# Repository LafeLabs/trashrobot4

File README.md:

# Trash Robot

- [arduinocode](arduinocode/)
- [circuitboards](circuitboards/)
- [samtec](samtec/)
- [power](power/)
- [dualhbridge](dualhbridge/)
- [enclosure](enclosure/)
- [unoshield](unoshield/)

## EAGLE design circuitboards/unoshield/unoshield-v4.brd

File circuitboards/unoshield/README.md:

# UNO Shield

- photo of board
- bill of materials excel file
- bill of materials html table
- digikey bom link
- links to arduino codes

[unoshield-v4.brd](unoshield-v4.brd)

[unoshield-v4.sch](unoshield-v4.sch)

[link up a level../](../)

[editor.php](editor.php)

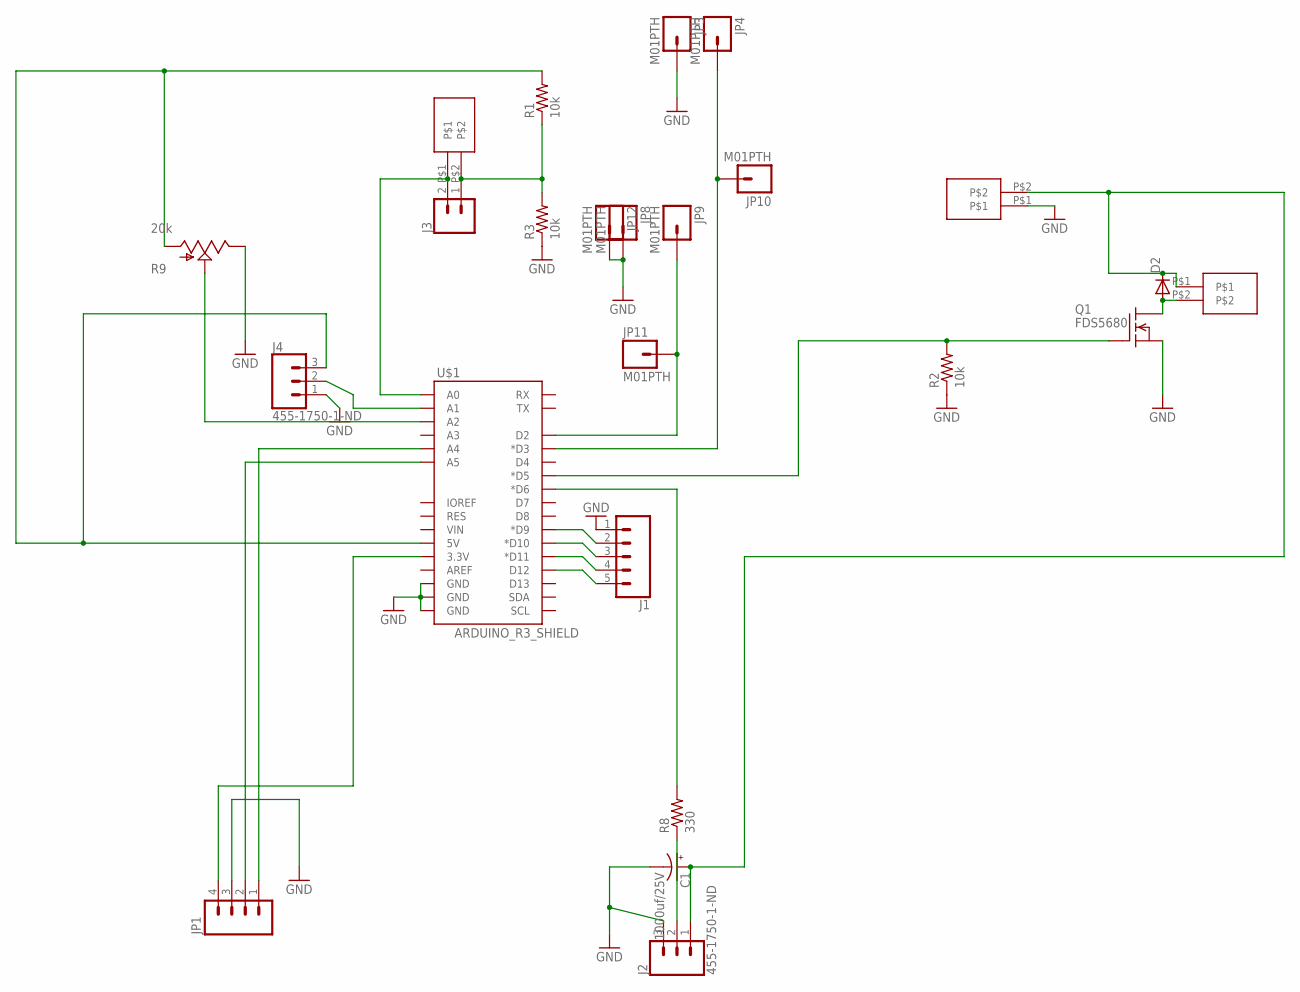
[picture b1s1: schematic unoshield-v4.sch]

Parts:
C1: 1000uf/25V; CPOL-RADIAL-1000UF-25V-KIT
D2: DIODE-DO-214AC; DO-214AC
J1: CONN_05; 1X05
J2, J4: 455-1750-1-ND; 1X03
J3: CONN_02; 1X02
JP1: M04PTH; 1X04
JP3, JP4, JP8, JP9, JP10, JP11, JP12: M01PTH; 1X01
Q1: FDS5680; SO-8
R1, R2, R3: 10k; R0603
R8: 330; R0603
R9: 20k; ALPS_POT_KIT
U$1: ARDUINO_R3_SHIELD; UNO_R3_SHIELD
U$6: SPRING-TERMINAL
X1, X2: SPRING-TERMINAL

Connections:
5V: J4.3, R1.2, R9.P$3 (A), U$1.5V
BUTTON: JP4.1, JP10.1, U$1.D3 (*D3)
CL: JP1.2, U$1.A5
DA: JP1.1, U$1.A4
GND: C1.-, J1.1, J2.3, J4.1, JP1.3, JP3.1, JP8.1, JP12.1, Q1.1 (S), Q1.2 (S), Q1.3 (S), R2.1, R3.1, R9.P$1 (E), U$1.GND@0 (GND), U$1.GND@1 (GND), U$1.GND@2 (GND), X1.P$1
unnamed: Q1.4 (G), R2.2, U$1.D5 (*D5)
unnamed: R8.2, U$1.D6 (*D6)
unnamed: J3.1, R1.1, R3.2, X2.P$2
unnamed: J4.2, U$1.A1
unnamed: J1.5, U$1.D12
unnamed: D2.A, Q1.5 (D), Q1.6 (D), Q1.7 (D), Q1.8 (D), U$6.P$2
unnamed: J1.4, U$1.D11 (*D11)
unnamed: J1.3, U$1.D10 (*D10)
unnamed: J1.2, U$1.D9 (*D9)
unnamed: JP9.1, JP11.1, U$1.D2
unnamed: J3.2, U$1.A0, X2.P$1
unnamed: J2.2, R8.1
unnamed: R9.P$2 (S), U$1.A2
VCC: JP1.4, U$1.3.3V
VIN: C1.+, D2.C, J2.1, U$6.P$1, X1.P$2

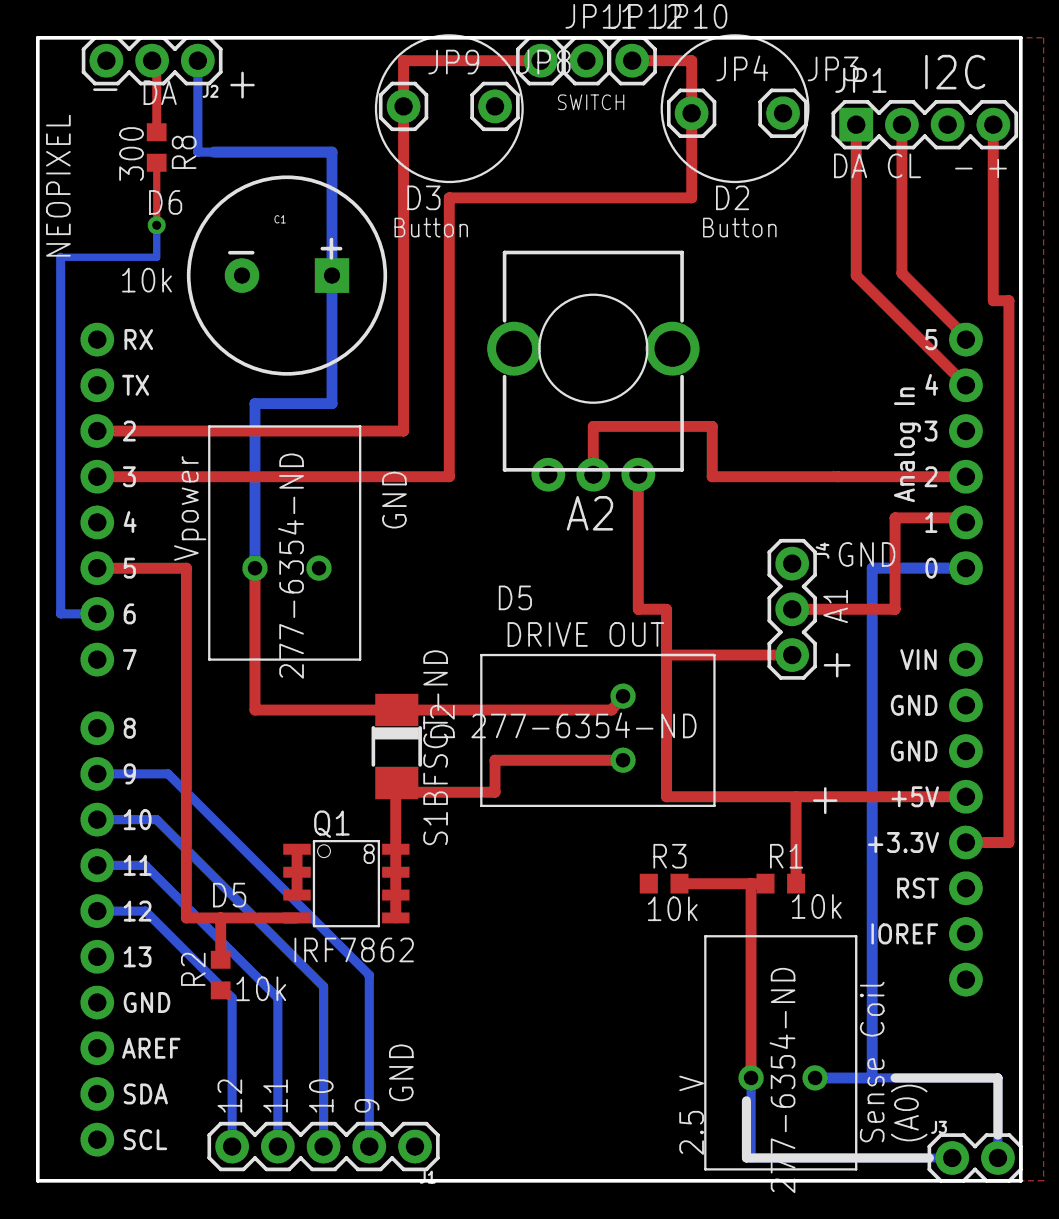
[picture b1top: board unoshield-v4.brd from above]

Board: 2 copper layers, 54.6 x 63.5 mm, 24 parts (0 on the bottom side), 20 nets.

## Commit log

2019-10-17 building out the new trash robot
2019-10-20 building index.html for arduino code documentation
2019-10-20 arduino code editor is now the real thing, sort of...
2019-10-25 putting together more of the arduino code
2019-10-30 working on the structure of the documtnetaiotnt
2019-10-30 adding a bunch of code, which is now tested with robot parts

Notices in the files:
parts and their libraries:
SparkFun-Boards: Licensing: Creative Commons ShareAlike 4.0 International - https://creativecommons.org/licenses/by-sa/4.0
